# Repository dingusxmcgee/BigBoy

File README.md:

# BigBoy
 BigBoy is a 6 key macropad with a rotary encoder and a big ol brass knob. The case and its parts were designed by me and the pcb was designed by tominabox.

Encoder used (EC21A1540401):
https://www.mouser.com/en/ProductDetail/Alps-Alpine/EC21A1540401?qs=YMSFtX0bdJDqJ3PNi4kFEA%3D%3D

Screws:

Case: m2.5 sockethead 5mm 
https://www.mcmaster.com/91292A009/

Bumpons: 8x2.5
https://www.amazon.com/Silicone-Rubber-Bumpons-Adhesive-Circles/dp/B07DN6W6VN/ref=sr_1_5?crid=3ADHACEENERSY&keywords=8mm%2Bbumpons&qid=1651329537&sprefix=8mm%2Bbumpon%2Caps%2C150&sr=8-5&th=1

Many thanks to tominabox for the pcb work and collaboration on this project!

*All files are provided as is and I accept no liability if they aren't very good.*

*These files were specifically designed to be milled by a CNC machine. Any other fabrication method may require modification*

*Licensed with Unlicense*

If you would like to support me in some way, consider [buying me a coffee :)](https://www.buymeacoffee.com/dingusxmcgee)

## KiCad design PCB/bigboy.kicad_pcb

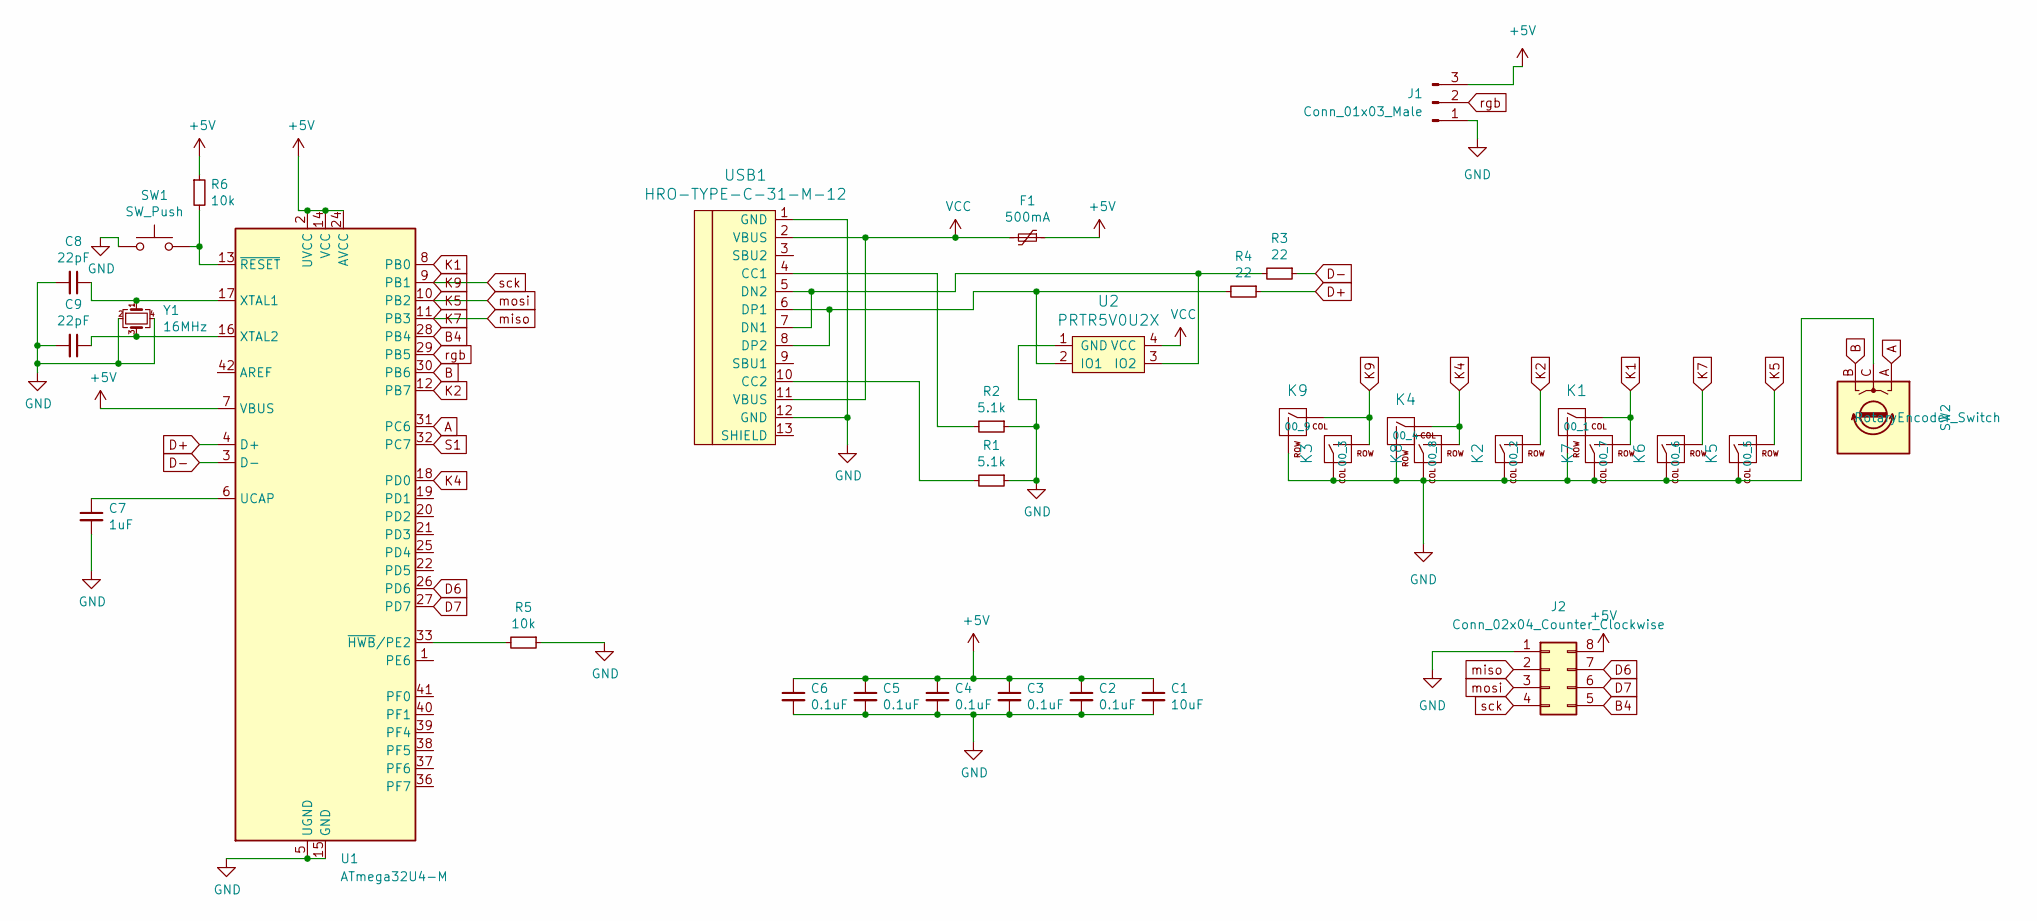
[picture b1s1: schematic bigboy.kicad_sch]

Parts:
C1: 10uF; C_0603_1608Metric
C2, C3, C4, C5, C6: 0.1uF; C_0603_1608Metric
C7: 1uF; C_0603_1608Metric
C8, C9: 22pF; C_0603_1608Metric
F1: 500mA; Fuse_1206_3216Metric
J1: Conn_01x03_Male; PinHeader_1x03_P2.54mm_Vertical
J2: Conn_02x04_Counter_Clockwise; PinHeader_2x04_P2.54mm_Vertical
K1, K2, K4, K5, K6, K9: 1U; MXOnly-1U-NoLED
K3, K7, K8: 1U; MXOnly-2U-NoLED
R1, R2: 5.1k; R_0603_1608Metric
R3, R4: 22; R_0603_1608Metric
R5, R6: 10k; R_0603_1608Metric
SW1: SW_Push; SKQG-1155865
SW2: RotaryEncoder_Switch; RotaryEncoder_EC11
U1: ATmega32U4-M; QFN-44-1EP_7x7mm_P0.5mm_EP5.2x5.2mm
U2: PRTR5V0U2X; SOT143B
USB1: HRO-TYPE-C-31-M-12; HRO-TYPE-C-31-M-12-Assembly
Y1: 16MHz; Crystal_SMD_3225-4Pin_3.2x2.5mm

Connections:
+5V: C1.1, C2.1, C3.1, C4.1, C5.1, C6.1, F1.1, J1.3, J2.8, R6.1, U1.2 (UVCC), U1.7 (VBUS), U1.14 (VCC), U1.24 (AVCC), U1.34 (VCC), U1.44 (AVCC)
A: SW2.A, U1.31 (PC6); also elsewhere on the board
B: SW2.B, U1.30 (PB6); also elsewhere on the board
B4: J2.5, U1.28 (PB4)
D6: J2.7, U1.26 (PD6)
D7: J2.6, U1.27 (PD7)
D+: R4.1, U1.4 (D+)
D-: R3.1, U1.3 (D-)
GND: C1.2, C2.2, C3.2, C4.2, C5.2, C6.2, C7.2, C8.2, C9.2, J1.1, J2.1, K1.2 (ROW), K2.1 (COL), K3.1 (COL), K4.2 (ROW), K5.1 (COL), K6.1 (COL), K7.1 (COL), K8.1 (COL), K9.2 (ROW), R1.1, R2.1, R5.1, SW1.1, SW2.C, U1.5 (UGND), U1.15 (GND), U1.23 (GND), U1.35 (GND), U1.43 (GND), U1.45 (GND), U2.1 (GND), USB1.1 (GND), USB1.12 (GND), Y1.2, Y1.4; also elsewhere on the board
K1: K1.1 (COL), K7.2 (ROW), U1.8 (PB0)
K2: K2.2 (ROW), U1.12 (PB7)
K4: K4.1 (COL), K8.2 (ROW), U1.18 (PD0)
K5: J2.3, K5.2 (ROW), U1.10 (PB2)
K7: J2.2, K6.2 (ROW), U1.11 (PB3)
K9: J2.4, K3.2 (ROW), K9.1 (COL), U1.9 (PB1)
unnamed: C7.1, U1.6 (UCAP)
unnamed: C8.1, U1.17 (XTAL1), Y1.1
unnamed: C9.1, U1.16 (XTAL2), Y1.3
unnamed: R1.2, USB1.10 (CC2)
unnamed: R2.2, USB1.4 (CC1)
unnamed: R3.2, U2.3 (IO2), USB1.5 (DN2), USB1.7 (DN1)
unnamed: R4.2, U2.2 (IO1), USB1.6 (DP1), USB1.8 (DP2)
unnamed: R5.2, U1.33 (~HWB/PE2)
unnamed: R6.2, SW1.2, U1.13 (~RESET)
S1: U1.32 (PC7)
VCC: F1.2, U2.4 (VCC), USB1.2 (VBUS), USB1.11 (VBUS)
rgb: J1.2, U1.29 (PB5)

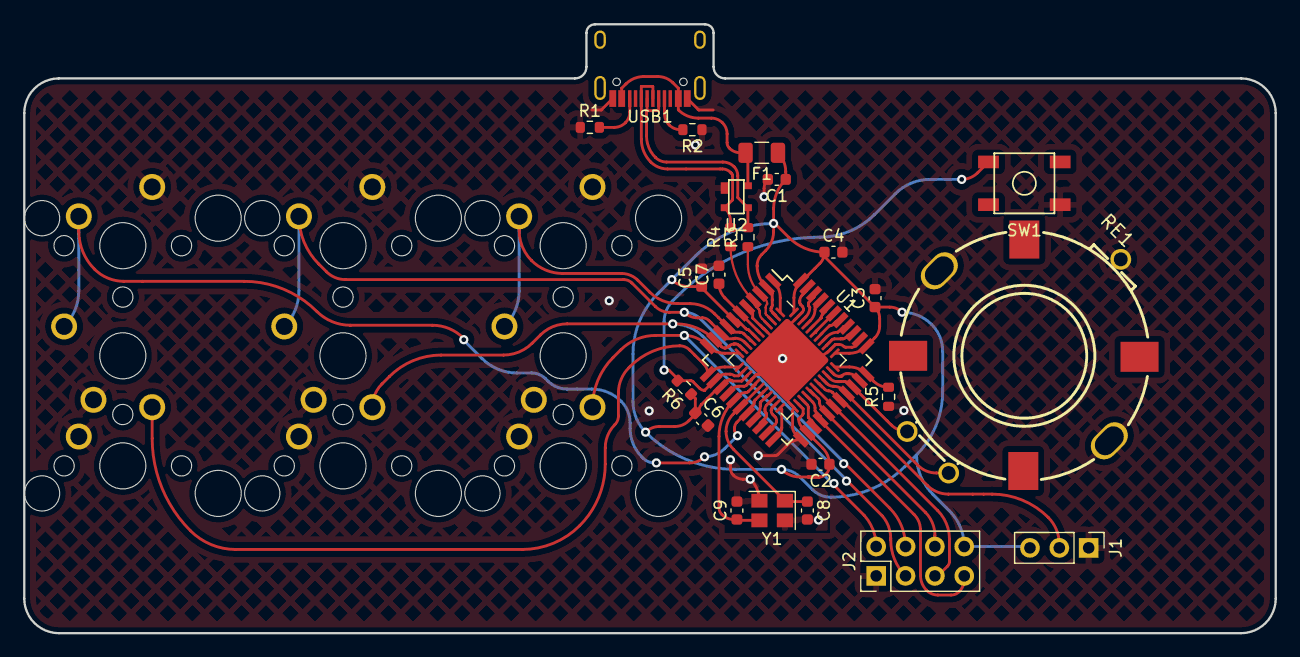
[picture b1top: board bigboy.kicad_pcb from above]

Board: 2 copper layers, 108.3 x 52.7 mm, 33 parts (0 on the bottom side), 26 nets.

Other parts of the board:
RE1: SW-TH_EC21A1540401

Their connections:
A: RE1.A; also elsewhere on the board
B: RE1.B; also elsewhere on the board
GND: RE1.C, RE1.D, RE1.E; also elsewhere on the board

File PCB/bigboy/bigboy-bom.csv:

Qty,Reference(s),Value,LibPart,Footprint,Datasheet,LCSC Part Number
1,C1,10uF,Device:C_Small,Capacitor_SMD:C_0603_1608Metric,,C19702
5,"C2, C3, C4, C5, C6",0.1uF,Device:C_Small,Capacitor_SMD:C_0603_1608Metric,,C14663
1,C7,1uF,Device:C_Small,Capacitor_SMD:C_0603_1608Metric,,C15849
2,"C8, C9",22pF,Device:C_Small,Capacitor_SMD:C_0603_1608Metric,,C1653
1,F1,500mA,Device:Polyfuse_Small,Fuse:Fuse_1206_3216Metric,,C151162
2,"R1, R2",5.1k,Device:R_Small,Resistor_SMD:R_0603_1608Metric,,C23186
2,"R3, R4",22,Device:R_Small,Resistor_SMD:R_0603_1608Metric,,C23345
2,"R5, R6",10k,Device:R_Small,Resistor_SMD:R_0603_1608Metric,,C25804
1,SW1,SW_Push,Switch:SW_Push,,,C2886894
1,U1,ATmega32U4-M,MCU_Microchip_ATmega:ATmega32U4-M,Package_DFN_QFN:QFN-44-1EP_7x7mm_P0.5mm_EP5.2x5.2mm,,C45874
1,U2,PRTR5V0U2X,random-keyboard-parts:PRTR5V0U2X,random-keyboard-parts:SOT143B,,C78442
1,USB1,HRO-TYPE-C-31-M-12,Type-C:HRO-TYPE-C-31-M-12,,,C167321
1,Y1,16MHz,Device:Crystal_GND24_Small,Crystal:Crystal_SMD_3225-4Pin_3.2x2.5mm,,C13738
1,RE1,EC21A1540401,,,,C231768

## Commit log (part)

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2022-03-28 First commit i guess
2022-04-30 Update with V2 files
2022-05-04 gitignore
